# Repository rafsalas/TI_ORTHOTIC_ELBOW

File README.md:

# TI_ORTHOTIC_ELBOW
##Compile and Run
Source code for this project exist in the src directory. Build and compile code for MSP432 on TI code composer. Mspware is required to run the project. After compillation flash it to the MSP432. 

Android code should be built and compiled on Android studio.

##Team Members
* David Cuevas (Student, Motor-Body Interface Lead) - david.cuevas@tamu.edu
* Nathan Glaser (Student, Body-Sensor Interface Lead) - cmdgnathan@tamu.edu 
* Joe Loredo (Student, Power Lead, User Interface Lead) -joelored@tamu.edu
* Rafael Salas (Student, Data Processing Lead) - rafsalas@tamu.edu
* Leonardo Estevez (Mentor, TI Contact) - Leonardo@ti.com

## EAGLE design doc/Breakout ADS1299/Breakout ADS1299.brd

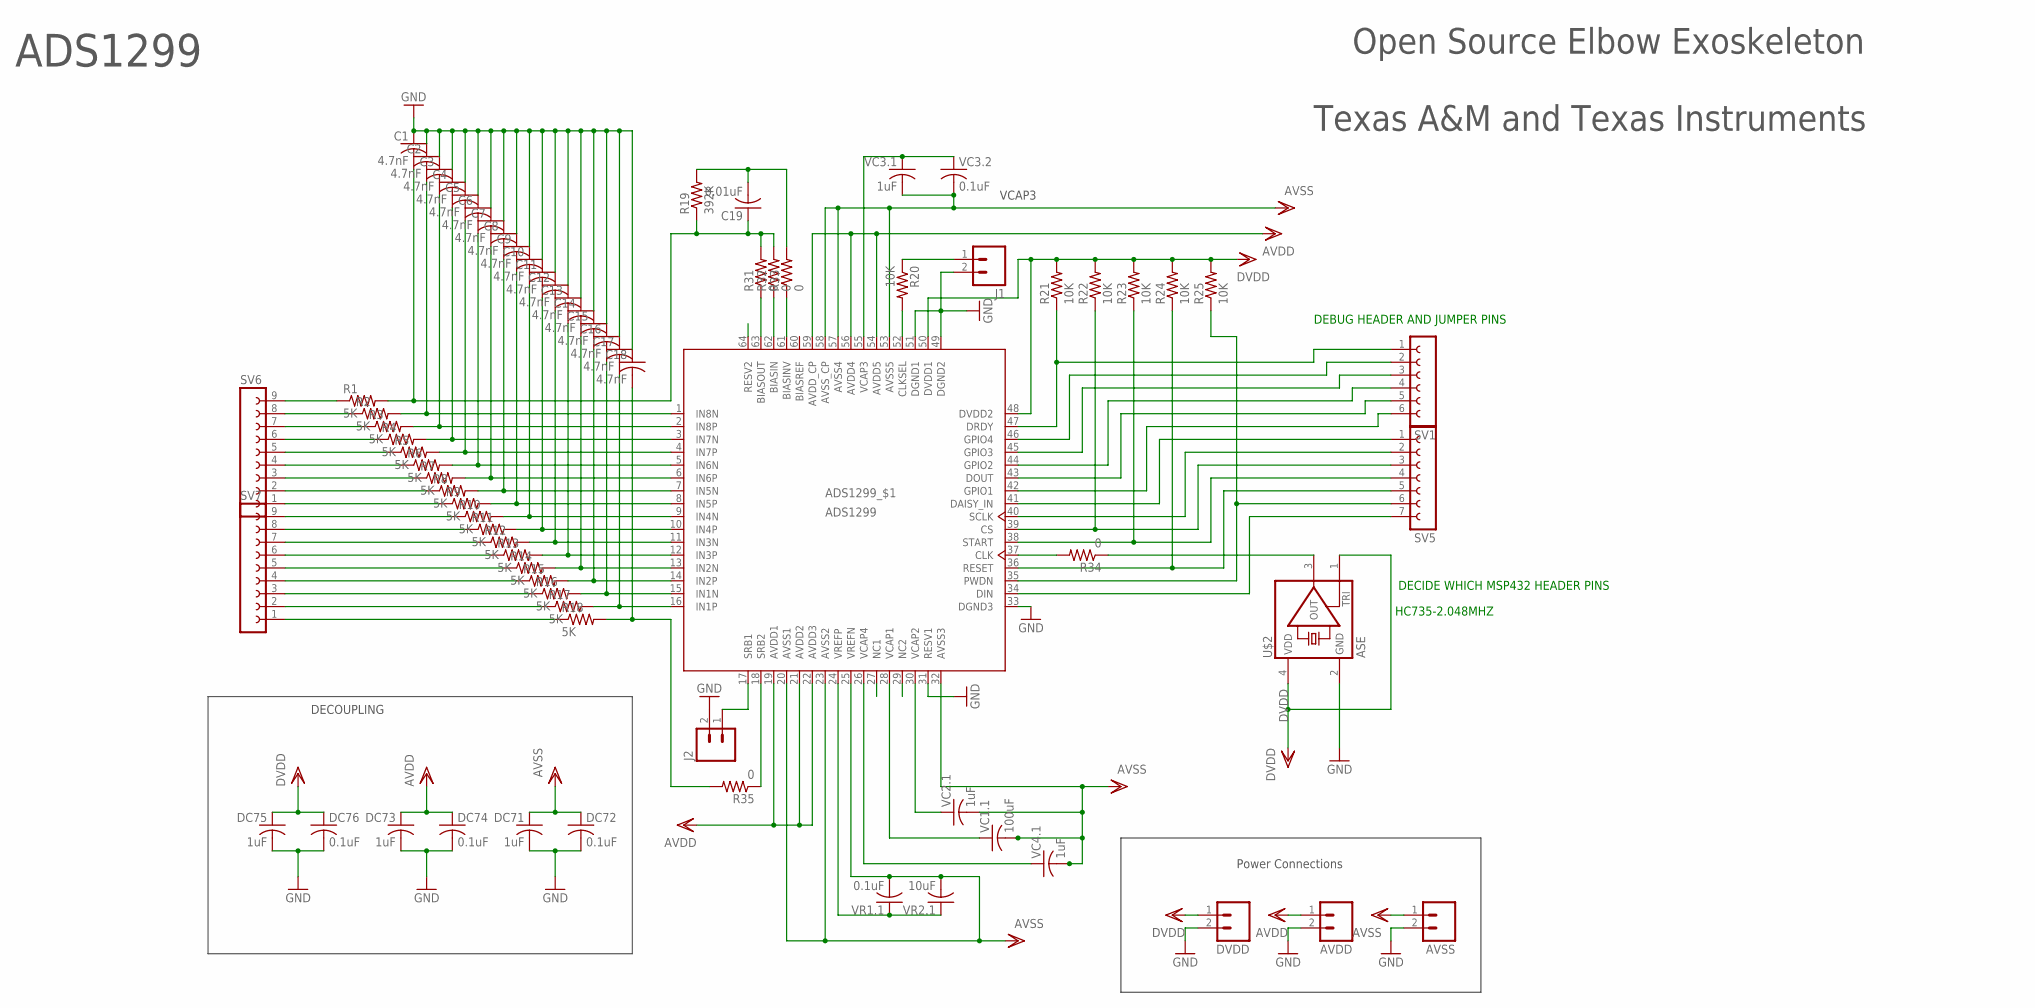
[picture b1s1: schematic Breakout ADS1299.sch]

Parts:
ADS1: ADS1299; PAG_S-PQFP-G64
AVDD: M025MM; SCREWTERMINAL-5MM-2
AVSS: M025MM; SCREWTERMINAL-5MM-2
C1, C2, C3, C4, C5, C6, C7, C8, C9, C10, C11, C12, C13, C14, C15, C16, C17, C18: 4.7nF; C0603
C19: 0.01uF; C0603
DC71, DC73, DC75: 1uF; C0603
DC72, DC74, DC76: 0.1uF; C0603
DVDD: M025MM; SCREWTERMINAL-5MM-2
J1, J2: M02PTH; 1X02
R1, R2, R3, R4, R5, R6, R7, R8, R9, R10, R11, R12, R13, R14, R15, R16, R17, R18: 5K; R0603
R19: 392K; R0603
R20, R21, R22, R23, R24, R25: 10K; R0603
R31, R32, R33, R34, R35: 0; R0603
SV1: FE06-1; FE06
SV5: FE07-1; FE07
SV6, SV7: FE09-1; FE09
U$2: ASE
VC1.1: 100uF; C0603
VC2.1, VC3.1, VC4.1: 1uF; C0603
VC3.2: 0.1uF; C0603
VR1.1: 0.1uF; C0603
VR2.1: 10uF; C0603

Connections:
AVDD: ADS1.19 (AVDD1), ADS1.21 (AVDD2), ADS1.22 (AVDD3), ADS1.54 (AVDD5), ADS1.56 (AVDD4), ADS1.59 (AVDD_CP), AVDD.1, DC73.1, DC74.1
AVSS: ADS1.20 (AVSS1), ADS1.23 (AVSS2), ADS1.25 (VREFN), ADS1.32 (AVSS3), ADS1.53 (AVSS5), ADS1.57 (AVSS4), ADS1.58 (AVSS_CP), AVSS.1, DC71.1, DC72.1, VC1.1.2, VC2.1.2, VC3.1.2, VC3.2.2, VC4.1.2, VR1.1.2, VR2.1.2
BIASIN: ADS1.62 (BIASIN), R32.1
BIASINV: ADS1.61 (BIASINV), R33.1
BIASINV_1: C19.2, R19.2, R33.2
BIASOUT: ADS1.63 (BIASOUT), R31.1
DAISY_IN: ADS1.41 (DAISY_IN), SV5.1
DVDD: ADS1.48 (DVDD2), ADS1.50 (DVDD1), DC75.1, DC76.1, DVDD.1, R21.2, R22.2, R23.2, R24.2, R25.2, U$2.1 (TRI), U$2.4 (VDD)
GND: ADS1.31 (RESV1), ADS1.33 (DGND3), ADS1.49 (DGND2), ADS1.51 (DGND1), AVDD.2, AVSS.2, C1.1, C2.1, C3.1, C4.1, C5.1, C6.1, C7.1, C8.1, C9.1, C10.1, C11.1, C12.1, C13.1, C14.1, C15.1, C16.1, C17.1, C18.1, DC71.2, DC72.2, DC73.2, DC74.2, DC75.2, DC76.2, DVDD.2, J1.2, J2.2, U$2.2 (GND)
GPIO1: ADS1.42 (GPIO1), SV1.6
GPIO2: ADS1.44 (GPIO2), SV1.4
GPIO3: ADS1.45 (GPIO3), SV1.3
GPIO4: ADS1.46 (GPIO4), SV1.2
unnamed: ADS1.34 (DIN), SV5.7
unnamed: ADS1.18 (SRB2), R35.1
unnamed: ADS1.37 (CLK), R34.2
unnamed: ADS1.55 (VCAP3), VC3.1.1, VC3.2.1
unnamed: ADS1.3 (IN7N), C4.2, R4.2
unnamed: ADS1.1 (IN8N), C2.2, R2.2
unnamed: ADS1.52 (CLKSEL), R20.2
unnamed: ADS1.5 (IN6N), C6.2, R6.2
unnamed: J1.1, R20.1
unnamed: ADS1.7 (IN5N), C8.2, R8.2
unnamed: ADS1.43 (DOUT), SV1.5
unnamed: ADS1.9 (IN4N), C10.2, R10.2
unnamed: C1.2, C19.1, R1.2, R19.1, R31.2, R32.2
unnamed: ADS1.11 (IN3N), C12.2, R12.2
unnamed: ADS1.40 (SCLK), SV5.2
unnamed: ADS1.13 (IN2N), C14.2, R14.2
unnamed: ADS1.15 (IN1N), C16.2, R16.2
unnamed: ADS1.24 (VREFP), VR1.1.1, VR2.1.1
unnamed: ADS1.26 (VCAP4), VC4.1.1
unnamed: ADS1.28 (VCAP1), VC1.1.1
unnamed: ADS1.30 (VCAP2), VC2.1.1
unnamed: R1.1, SV6.9
unnamed: R2.1, SV6.8
unnamed: R3.1, SV6.7
unnamed: R4.1, SV6.6
unnamed: R5.1, SV6.5
unnamed: R6.1, SV6.4
unnamed: R7.1, SV6.3
unnamed: R8.1, SV6.2
unnamed: R9.1, SV6.1
unnamed: R10.1, SV7.9
unnamed: R11.1, SV7.8
unnamed: R12.1, SV7.7
unnamed: R13.1, SV7.6
unnamed: R14.1, SV7.5
unnamed: R15.1, SV7.4
unnamed: R16.1, SV7.3
unnamed: R17.1, SV7.2
unnamed: R18.1, SV7.1
unnamed: ADS1.2 (IN8P), C3.2, R3.2
unnamed: ADS1.4 (IN7P), C5.2, R5.2
unnamed: ADS1.6 (IN6P), C7.2, R7.2
unnamed: ADS1.8 (IN5P), C9.2, R9.2
unnamed: ADS1.10 (IN4P), C11.2, R11.2
unnamed: ADS1.12 (IN3P), C13.2, R13.2
unnamed: ADS1.14 (IN2P), C15.2, R15.2
unnamed: ADS1.16 (IN1P), C17.2, R17.2
RST: ADS1.36 (RESET), R24.1, SV5.5
SRB1: ADS1.17 (SRB1), J2.1
_CLK: R34.1, U$2.3 (OUT)
_CS1: ADS1.39 (CS), R22.1, SV5.3
_DRDY: ADS1.47 (DRDY), R21.1, SV1.1
_PD: ADS1.35 (PWDN), R25.1, SV5.6
_SRB2: C18.2, R18.2, R35.2
_STRT: ADS1.38 (START), R23.1, SV5.4

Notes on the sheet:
VCAP3
DECOUPLING
HC735-2.048MHZ
DECIDE WHICH MSP432 HEADER PINS
DEBUG HEADER AND JUMPER PINS
ADS1299
Open Source Elbow Exoskeleton
Texas A&M and Texas Instruments
Power Connections

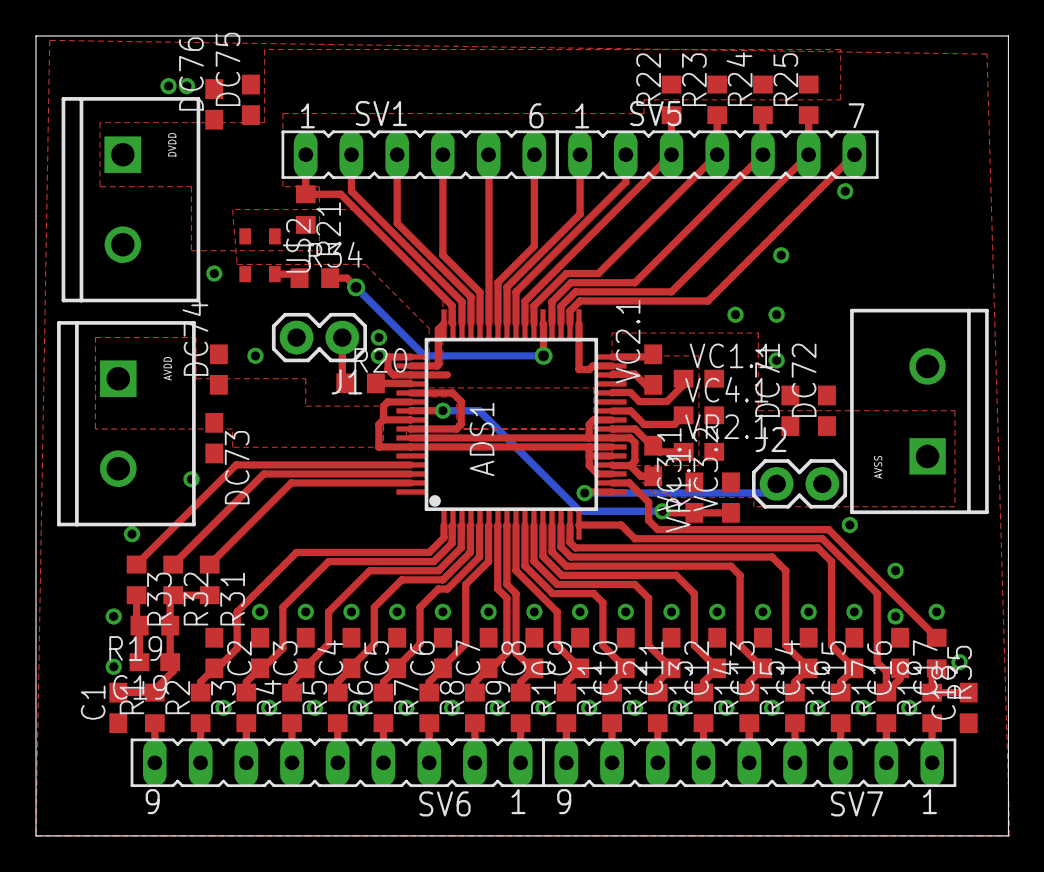
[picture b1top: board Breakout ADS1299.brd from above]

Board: 2 copper layers, 54.0 x 44.4 mm, 73 parts (0 on the bottom side), 68 nets.

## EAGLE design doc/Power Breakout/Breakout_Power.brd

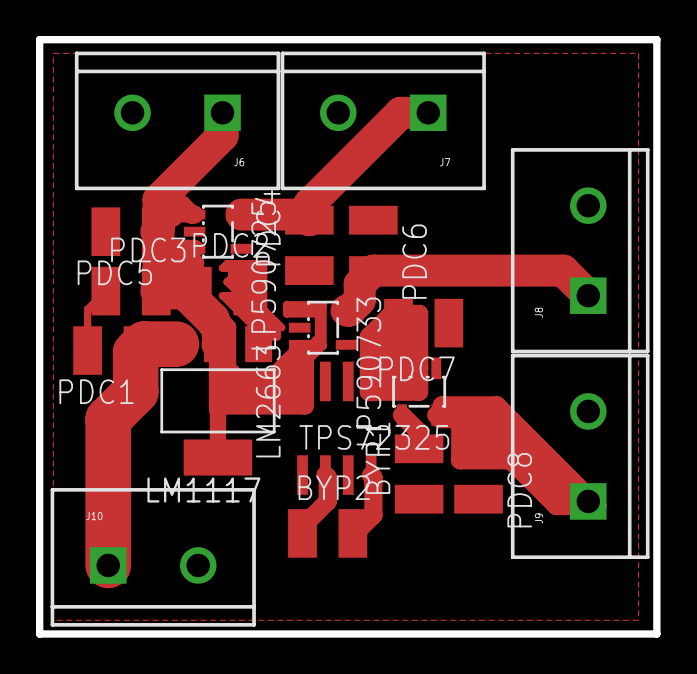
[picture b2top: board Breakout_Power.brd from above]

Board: 2 copper layers, 34.3 x 33.0 mm, 20 parts (0 on the bottom side), 11 nets.

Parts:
BYP1: 0.01uF; C1210
BYP2: 47uF; C1210
J6: +3V3; SCREWTERMINAL-5MM-2
J7: AVDD; SCREWTERMINAL-5MM-2
J8: DVDD; SCREWTERMINAL-5MM-2
J9: AVSS; SCREWTERMINAL-5MM-2
J10: +5V; SCREWTERMINAL-5MM-2
LM1117: LM1117; SOT223
LM2663: LM2663; SO-08
LP590725: LP590725; SOT23-DBV
LP590733: LP590733; SOT23-DBV
PDC1: 10uF; C1210
PDC2: 100uF; C1210
PDC3, PDC4, PDC5, PDC6: 1uF; C1210
PDC7: 47uF; C1210
PDC8: 2.2uF; C1210
TPS72325: TPS723XX25; SOT23-DBV

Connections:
+3V3: J6.1, LM1117.2, LM2663.8, LP590725.1, LP590733.1, PDC3.2, PDC5.1
+5V: J10.1, LM1117.3, PDC1.1
-3V3: LM2663.5, PDC7.2, TPS72325.2
AVDD: J7.1, LP590725.5, PDC4.2
AVSS: J9.1, TPS72325.5
DVDD: J8.1, LP590733.5, PDC6.2
GND: BYP1.1, J6.2, J7.2, J8.2, J9.2, J10.2, LM1117.1, LM2663.1, LM2663.6, LP590725.2, LP590733.2, PDC1.2, PDC2.2, PDC3.1, PDC4.1, PDC5.2, PDC6.1, PDC8.2, TPS72325.1
unnamed: LM1117.4, PDC2.1
unnamed: BYP1.2, TPS72325.4
unnamed: BYP2.1, LM2663.2
unnamed: BYP2.2, LM2663.4

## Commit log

2015-10-04 Adding code for class
2015-10-04 Adding Matlab analysis code
2015-10-04 Matlab Serial Port Test Code
2015-10-04 Moved to a different folder
2015-10-04 UART Test Code Upload
2015-10-08 Adding directories.
2015-10-08 Organizing Matlab Analysis files
2015-10-10 10/10 Matlab Code Update
2015-10-13 Adding matlab script to plot acc data
2015-11-05 Watch code added
2015-11-05 Matlab UART / GUI Trials 11/5
2015-11-06 SPI code added
2015-11-07 stuffs
2015-11-12 cleaning up
2015-11-12 clean
2015-11-12 cleaning source files
2015-11-12 Cleaned source directory
2015-11-19 Two's compliment and spi stuffs
2015-11-22 Added printf suppurt and fixed all Uart issues
2015-11-30 radial encoder code added and modifications to main
2016-02-01 modern changes
2016-02-01 poop
2016-02-01 stuff
2016-02-17 new spi files
2016-02-21 motor driver code added
2016-02-21 main file cleaned up
2016-02-24 working motor driver code added
2016-03-12 adding comment
2016-03-16 Removed excess skeleton code from main. Added ADS1299 modular read command. Pooped on Raf's implementation of 2's complement.
2016-03-21 Removed excess code fragments. Incorporated high pass, band stop, moving average, and normalization.
2016-03-23 250Hz interrupt added
2016-03-23 shit needs testing
2016-03-23 tests for timing spi collection
2016-03-24 EMG Sensor Routine Complete
2016-03-24 push
2016-03-25 interrupt changes
2016-03-25 Modified windowed filter
2016-03-25 basic framework modificatios
2016-03-25 Architecture summary
2016-03-25 added enable/disable inter.. Also modified drdy interrupt so that Drdy=pin
2016-03-25 added clk table
2016-03-25 optimization with MAP
2016-03-25 Nathans mods
2016-03-25 removing interrupt functions
2016-03-26 uart clock manipulation modification
2016-03-26 temporary commit
2016-03-27 temp
2016-03-28 SPI Timing
2016-03-28 Deleted Unnecessary folders
2016-03-28 Added files via upload
2016-03-28 stuff changes
2016-03-28 destroy
2016-03-29 one code to rule them all
2016-04-03 Main detail added SPI Comms Windowed Function Radial Encoder Angle Limiters
2016-04-03 changes to uart for clock and baud rate, new adc files, modifications to other files for testing
2016-04-06 Calibraton Phone App
2016-04-06 got rid of sports watch anf modified uart comms
2016-04-06 Updated transmitted message
2016-04-08 Update .gitignore
    remove xml from git ignore
2016-04-08 Update .gitignore
    remove xml from ignore
2016-04-08 ADS1299 Data Tests
2016-04-08 Layout file push
2016-04-09 Transmit stuff
2016-04-09 fixing merge issues and modifying uart file
2016-04-09 added cal features
2016-04-09 added comparator code
2016-04-13 adding changes made at blitz
2016-04-13 adjusting test code and deletng useless codes. Also modified drv8 motor driver file to handle direction condition
2016-04-14 minor comment modifications, maybe some other stuffs
2016-04-16 ADS1299 EMG Signal Test
2016-04-17 minor changes
2016-04-17 ADS1299 EMG Updates Combining
2016-04-17 Motor Test Preparations
2016-04-18 minor change
2016-04-18 4/17 update
    cosmetic changes
2016-04-18 Bluetooth Tested Calibration Routine Demo Routines
2016-04-18 minor issue
2016-04-19 Angle Demo Routine EMG Demo Routine
2016-04-20 testing complete
2016-04-20 Finalized Integration Finalized Comparator
2016-04-25 Corrected calibration motor shut off
2016-05-07 formating codes
2016-05-17 name changes

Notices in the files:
parts and their libraries:
SparkFun-Connectors: Licensing: Creative Commons ShareAlike 4.0 International - https://creativecommons.org/licenses/by-sa/4.0
